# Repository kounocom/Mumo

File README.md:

# Mumo - Compact ICM-45686+QMC6309H Module

A compact 13×18mm IMU module featuring the TDK InvenSense ICM-45686 6-axis IMU with integrated 32.768kHz clock and QST QMC6309H 3-axis magnetometer.

## Features

- **Compact Design**: 13×18mm form factor
- **High-Performance IMU**: TDK InvenSense ICM-45686 6-axis IMU with integrated 32.768kHz clock for precise output timesteps
- **3-Axis Magnetometer**: QST QMC6309H for 9-DOF sensing
- **Connectivity**: Castellated holes for flat mounting on compatible carrier PCBs
- **Power Optimization**: Solder bridges to disconnect I2C pull-ups for improved power efficiency when using SPI
- **Easily Configurable I2C Address**: Solder bridge for SD0 pin to change I2C address from `0x69` to `0x68`

## Compatibility

The pinout is **mostly compatible** with popular BMI160 and LSM6DS3 modules found on Amazon and AliExpress, with these differences:

- **OSDO**: Functions as VIN on AliExpress modules
- **CLK_CTL**: Not present on AliExpress modules

## Schematic

## Ordering Information

### Important Notes

⚠️ **IMU Pin 7**: Pin 7 of the IMU is intentionally disconnected as recommended for the ICM-45686. If substituting with another IMU that requires pin 7 as GND, modify the PCB to connect IMU pin 7 to ground.

⚠️ **Surface Finish**: ENIG surface finish is recommended for easier soldering and better reliability with the BGA magnetometer.

⚠️ **Castellated Holes**: While castellated holes significantly increase manufacturing cost, they enable flat soldering onto carrier boards. Consider your application requirements before deciding to omit them.

## License

See [LICENSE.md](LICENSE.md) for license information.

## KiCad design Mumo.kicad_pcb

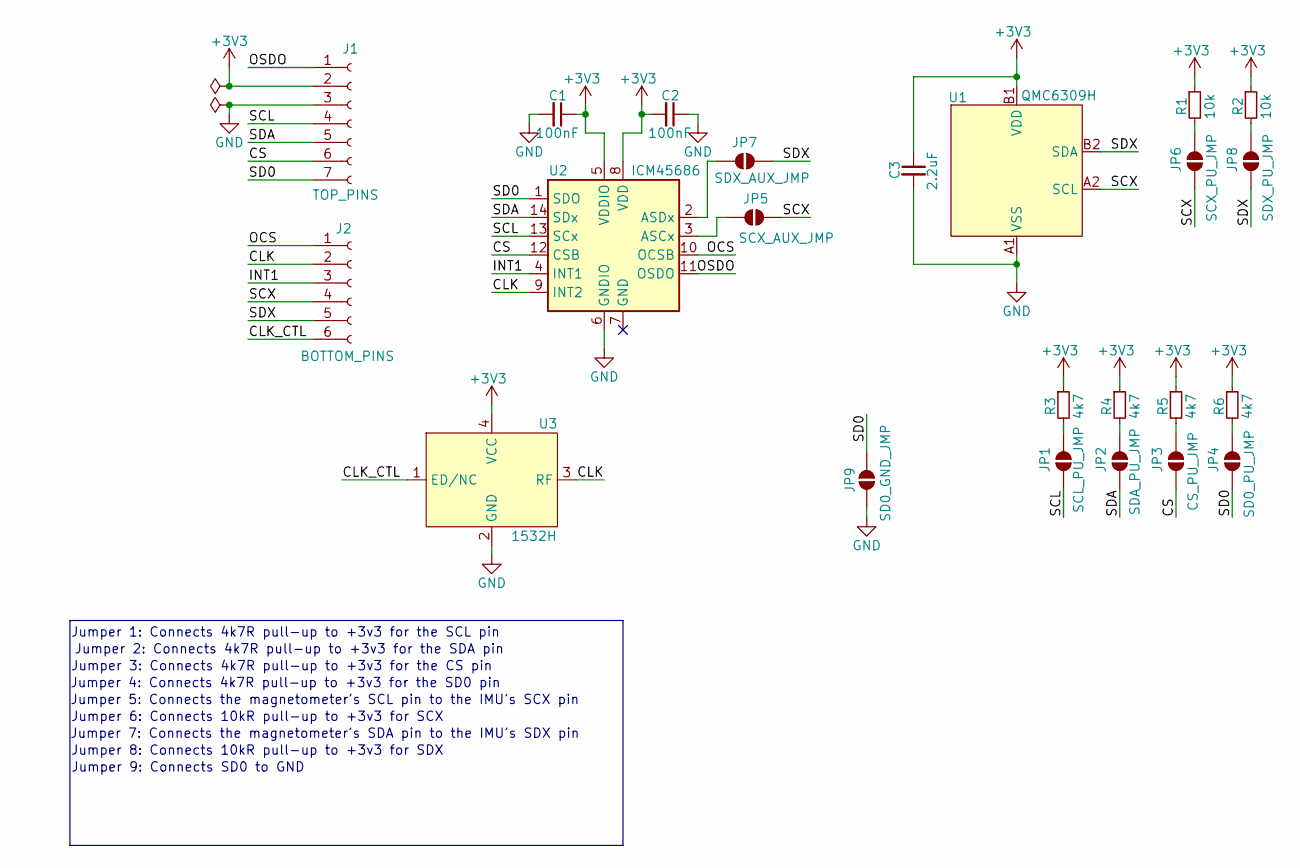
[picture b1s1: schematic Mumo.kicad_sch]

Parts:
C1, C2: 100nF; C_0402; MPN C1525
C3: 2.2uF; C_0603; MPN C57895
J1: TOP_PINS; TopPins; MPN N/A
J2: BOTTOM_PINS; BottomPins
JP1: SCL_PU_JMP; JMP_CLSD
JP2: SDA_PU_JMP; JMP_CLSD
JP3: CS_PU_JMP; JMP_CLSD
JP4: SD0_PU_JMP; JMP_CLSD
JP5: SCX_AUX_JMP; JMP_CLSD
JP6: SCX_PU_JMP; JMP_CLSD
JP7: SDX_AUX_JMP; JMP_CLSD
JP8: SDX_PU_JMP; JMP_CLSD
JP9: SD0_GND_JMP; JMP; MPN N/A
R1, R2: 10k; R_0402; MPN C25744
R3, R4, R5, R6: 4k7; R_0402; MPN C25900
U1: QMC6309H; QMC6309; MPN C49327200
U2: ICM45686; IMU; MPN C22459454
U3: 1532H; CLK; MPN C709192

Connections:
+3V3: C1.1, C2.2, C3.1, J1.2, R1.1, R2.1, R3.1, R4.1, R5.1, R6.1, U1.B1 (VDD), U2.5 (VDDIO), U2.8 (VDD), U3.4 (VCC)
/CLK: J2.2, U2.9 (INT2), U3.3 (RF)
/CLK_CTL: J2.6, U3.1 (ED/NC)
/CS: J1.6, JP3.1 (A), U2.12 (CSB)
/INT1: J2.3, U2.4 (INT1)
/OCS: J2.1, U2.10 (OCSB)
/OSDO: J1.1, U2.11 (OSDO)
/SCL: J1.4, JP1.1 (A), U2.13 (SCx)
/SCX: J2.4, JP5.2 (B), JP6.1 (A), U1.A2 (SCL)
/SD0: J1.7, JP4.1 (A), JP9.2 (B), U2.1 (SDO)
/SDA: J1.5, JP2.1 (A), U2.14 (SDx)
/SDX: J2.5, JP7.2 (B), JP8.1 (A), U1.B2 (SDA)
GND: C1.2, C2.1, C3.2, J1.3, JP9.1 (A), U1.A1 (VSS), U2.6 (GNDIO), U3.2 (GND)
unnamed: JP1.2 (B), R3.2
unnamed: JP2.2 (B), R4.2
unnamed: JP3.2 (B), R5.2
unnamed: JP4.2 (B), R6.2
unnamed: JP5.1 (A), U2.3 (ASCx)
unnamed: JP6.2 (B), R1.2
unnamed: JP7.1 (A), U2.2 (ASDx)
unnamed: JP8.2 (B), R2.2

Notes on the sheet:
Jumper 9: Connects SD0 to GND
Jumper 2: Connects 4k7R pull-up to +3v3 for the SDA pin
Jumper 7: Connects the magnetometer's SDA pin to the IMU's SDX pin
Jumper 5: Connects the magnetometer's SCL pin to the IMU's SCX pin
Jumper 6: Connects 10kR pull-up to +3v3 for SCX
Jumper 4: Connects 4k7R pull-up to +3v3 for the SD0 pin
Jumper 3: Connects 4k7R pull-up to +3v3 for the CS pin
Jumper 8: Connects 10kR pull-up to +3v3 for SDX
Jumper 1: Connects 4k7R pull-up to +3v3 for the SCL pin

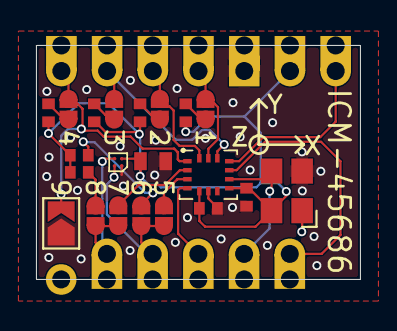
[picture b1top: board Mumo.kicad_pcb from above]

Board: 4 copper layers, 18.0 x 13.0 mm, 23 parts (0 on the bottom side), 21 nets.

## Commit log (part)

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2025-07-24 Initial
2026-01-03 v1.1
2026-01-03 update it again!!!!!!!!!!!!!!!!!!!!!!
